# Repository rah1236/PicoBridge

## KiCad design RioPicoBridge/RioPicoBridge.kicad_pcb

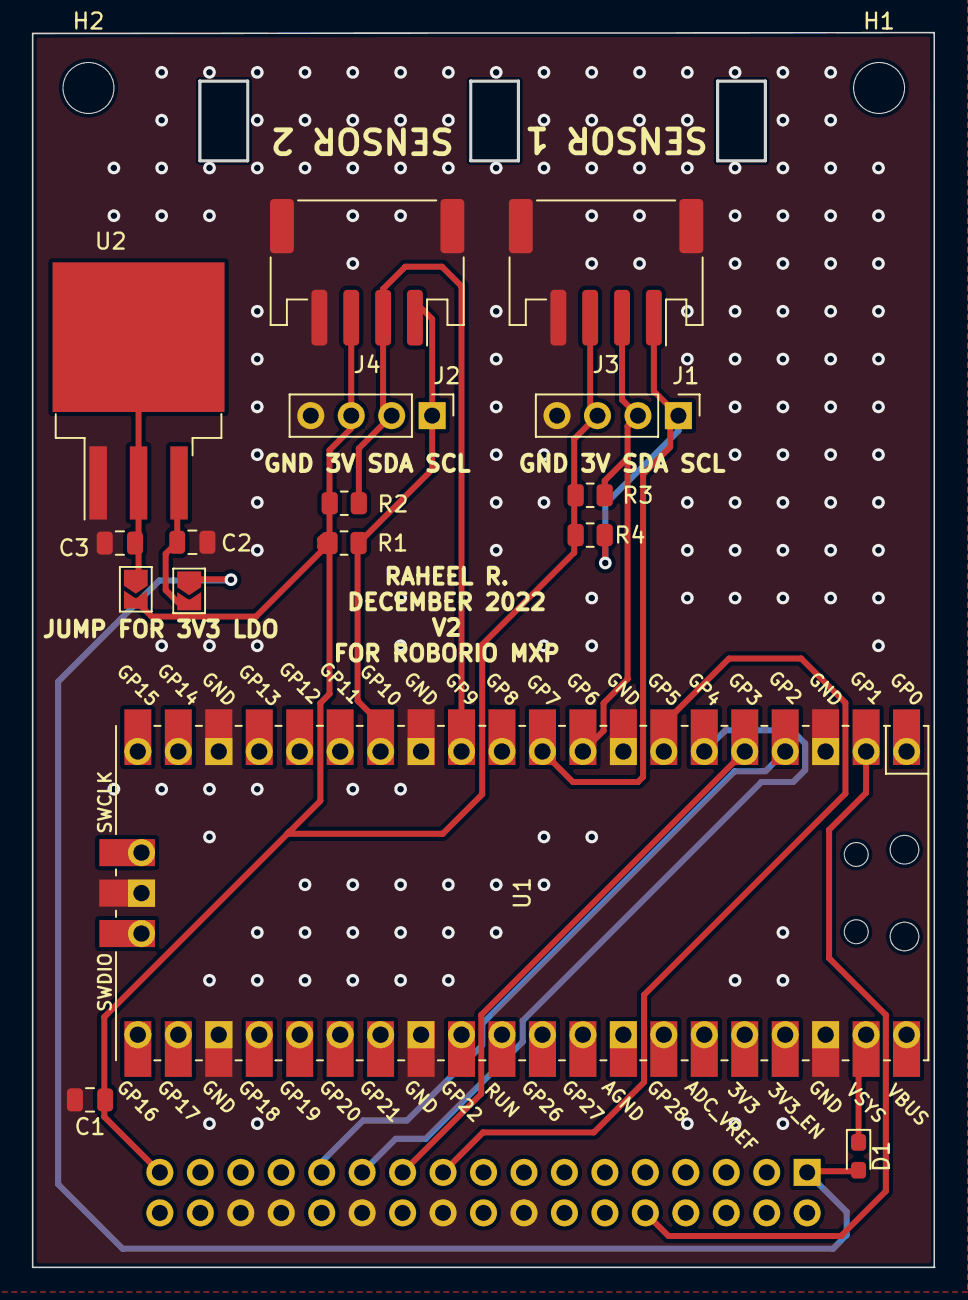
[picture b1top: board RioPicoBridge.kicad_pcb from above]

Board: 2 copper layers, 56.5 x 77.4 mm, 19 parts (1 on the bottom side), 15 nets.

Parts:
C1, C2: 10uF; C_0805_2012Metric
C3: 100uF; C_0805_2012Metric
D1: D_Schottky; D_0603_1608Metric_Pad1.05x0.95mm_HandSolder
H1, H2: MountingHole; MountingHole_3.2mm_M3
J1, J2: DUPONT; PinHeader_1x04_P2.54mm_Vertical
J3, J4: JST; JST_PH_S4B-PH-SM4-TB_1x04-1MP_P2.00mm_Horizontal
J5: MXP; PinSocket_2x17_P2.54mm_Vertical
JP1, JP2: Jumper_2_Open; SolderJumper-2_P1.3mm_Open_TrianglePad1.0x1.5mm
R1, R2, R3, R4: 4.7k; R_0805_2012Metric
U1: Pico; RPi_Pico_SMD_TH
U2: LM1117-3.3; TO-263-3_TabPin2

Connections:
+3V3: C1.1, J1.3, J2.3, J3.3, J4.3, J5.33, JP2.2 (B), R1.2, R2.2, R3.2, R4.2
+5V: D1.2 (A), J5.1, JP1.1 (A)
/CIPO: J5.23, U1.6 (GPIO4)
/COPI: J5.25, U1.4 (GPIO2)
/RIO_RX: J5.10, U1.2 (GPIO1)
/SCL1: J1.1, J3.1, R4.1, U1.10 (GPIO7)
/SCL2: J2.1, J4.1, R1.1, U1.14 (GPIO10)
/SCLK: J5.21, U1.5 (GPIO3)
/SDA1: J1.2, J3.2, R3.1, U1.9 (GPIO6)
/SDA2: J2.2, J4.2, R2.1, U1.12 (GPIO9)
/S_CS: J5.19, U1.7 (GPIO5)
GND: C1.2, C2.2, C3.2, J1.4, J2.4, J3.4, J3.MP, J4.4, J4.MP, J5.16, J5.20, J5.24, J5.28, J5.30, U1.3 (GND), U1.8 (GND), U1.13 (GND), U1.18 (GND), U1.23 (GND), U1.28 (GND), U1.38 (GND), U1.42 (GND), U2.1 (GND)
unnamed: C2.1, JP1.2 (B), U2.3 (VI)
unnamed: C3.1, JP2.1 (A), U2.2 (VO)
unnamed: D1.1 (K), U1.39 (VSYS)

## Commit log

2022-11-30 first first commit
2022-12-27 forgot to add gerbers
